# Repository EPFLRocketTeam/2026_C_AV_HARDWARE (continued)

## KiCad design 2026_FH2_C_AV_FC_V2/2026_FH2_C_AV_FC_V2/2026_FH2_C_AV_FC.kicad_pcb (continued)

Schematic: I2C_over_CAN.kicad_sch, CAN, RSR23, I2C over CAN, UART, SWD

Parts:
C57, C58, C59, C60, C61, C62, C63, C67, C68: 100n; C_0603_1608Metric; Mouser Part Number 581-06035C104JAT2A
C64: 2u2; C_0603_1608Metric; Mouser Part Number 581-06036D225K
C65, C66, C69, C70: 47p; C_0603_1608Metric; Mouser Part Number 581-06033A470GAT2A
D29: PESD4USB3UTBS; PESD4USB3UTBSQX; Mouser Part Number 771-PESD4USB3UTBS-QX
D31, D35: DESD2CAN2SOQ-7; SOT96P240X110-3N; Mouser Part Number 621-DESD2CAN2SOQ-7
R56, R57, R60, R63: 120; R_0603_1608Metric; Mouser Part Number 603-RC0603FR-13120RL
R58, R59: 33; R_0402_1005Metric; Mouser Part Number 603-RC0402FR-7D33RL
R61, R62: 33; R_0603_1608Metric; Mouser Part Number 603-RC0603FR-7W33RL
R76: 10k; R_0603_1608Metric; Mouser Part Number 603-AC0603FRE0710KL
TP5: CANSDAL; TestPoint_THTPad_1.0x1.0mm_Drill0.5mm
TP6: CANSCLL; TestPoint_THTPad_1.0x1.0mm_Drill0.5mm
TP7: CANSDAH; TestPoint_THTPad_1.0x1.0mm_Drill0.5mm
TP8: CANSCLH; TestPoint_THTPad_1.0x1.0mm_Drill0.5mm
TP9: SCL; TestPoint_THTPad_1.0x1.0mm_Drill0.5mm
TP10: SDA; TestPoint_THTPad_1.0x1.0mm_Drill0.5mm
TP11, TP13: CANH; TestPoint_THTPad_1.0x1.0mm_Drill0.5mm
TP12, TP14: CANL; TestPoint_THTPad_1.0x1.0mm_Drill0.5mm
U12: MAX3226; SSOP-16_5.3x6.2mm_P0.65mm; Mouser Part Number 700-MAX3226EAET
U13: SPINE_LT3960; LT3960; Mouser Part Number 584-LT3960EMSE#PBF; Mouser ID 584-LT3960EMSE#PBF
U14, U15: MCP2542FDxMF; DFN-8-1EP_3x3mm_P0.65mm_EP1.55x2.4mm; Mouser Part Number 579-MCP2542FD-E/MF

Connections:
+3V3: C58.1, C62.2, C64.1, C67.2, R76.2, U12.15 (VCC), U12.16 (~FORCEOFF), U13.6 (VIN), U13.8 (VCC), U14.5 (VIO), U15.5 (VIO); also elsewhere on the board
+5V: C63.1, C68.1, U14.3 (VDD), U15.3 (VDD); also elsewhere on the board
/Project Architecture/CAN RS232 and other connections/CAN1_H: C66.1, D31.1, R60.2, TP11.1, U14.7 (CANH); also elsewhere on the board
/Project Architecture/CAN RS232 and other connections/CAN1_L: C65.1, D31.2, R60.1, TP12.1, U14.6 (CANL); also elsewhere on the board
/Project Architecture/CAN RS232 and other connections/CAN2_H: C70.1, D35.1, R63.2, TP13.1, U15.7 (CANH); also elsewhere on the board
/Project Architecture/CAN RS232 and other connections/CAN2_L: C69.1, D35.2, R63.1, TP14.1, U15.6 (CANL); also elsewhere on the board
/Project Architecture/CAN RS232 and other connections/CANSCLH: D29.4, D29.7, R57.2, TP8.1, U13.4 (CANSCLH); also elsewhere on the board
/Project Architecture/CAN RS232 and other connections/CANSCLL: D29.5, D29.6, R57.1, TP6.1, U13.5 (CANSCLL); also elsewhere on the board
/Project Architecture/CAN RS232 and other connections/CANSDAH: D29.2, D29.9, R56.1, TP7.1, U13.2 (CANSDAH); also elsewhere on the board
/Project Architecture/CAN RS232 and other connections/CANSDAL: D29.1, D29.10, R56.2, TP5.1, U13.1 (CANSDAL); also elsewhere on the board
/Project Architecture/CAN RS232 and other connections/CAN_RX_1: R59.1; also elsewhere on the board
/Project Architecture/CAN RS232 and other connections/CAN_RX_2: R62.1; also elsewhere on the board
/Project Architecture/CAN RS232 and other connections/CAN_TX_1: R58.1; also elsewhere on the board
/Project Architecture/CAN RS232 and other connections/CAN_TX_2: R61.1; also elsewhere on the board
/Project Architecture/CAN RS232 and other connections/RX_RS232: U12.8 (R1IN); also elsewhere on the board
/Project Architecture/CAN RS232 and other connections/SCL: TP9.1, U13.9 (SCL); also elsewhere on the board
/Project Architecture/CAN RS232 and other connections/SDA: TP10.1, U13.10 (SDA); also elsewhere on the board
/Project Architecture/CAN RS232 and other connections/TX_RS232: U12.13 (T1OUT); also elsewhere on the board
/Project Architecture/CAN RS232 and other connections/rx_uart: U12.9 (R1OUT); also elsewhere on the board
/Project Architecture/CAN RS232 and other connections/tx_uart: U12.11 (T1IN); also elsewhere on the board
GND: C58.2, C60.2, C61.2, C62.1, C63.2, C64.2, C65.2, C66.2, C67.1, C68.2, C69.2, C70.2, D29.3, D29.8, D31.3, D35.3, U12.12 (FORCEON), U12.14 (GND), U13.3 (GND), U13.11 (GND), U14.2 (VSS), U14.8 (STBY), U14.9 (VSS), U15.2 (VSS), U15.8 (STBY), U15.9 (VSS); also elsewhere on the board
unnamed: C57.1, U12.2 (C1+)
unnamed: C57.2, U12.4 (C1-)
unnamed: C59.1, U12.5 (C2+)
unnamed: C59.2, U12.6 (C2-)
unnamed: C61.1, U12.3 (V+)
unnamed: C60.1, U12.7 (V-)
unnamed: R76.1, U13.7 (EN/MODE)
unnamed: R59.2, U14.4 (RXD)
unnamed: R58.2, U14.1 (TXD)
unnamed: R62.2, U15.4 (RXD)
unnamed: R61.2, U15.1 (TXD)

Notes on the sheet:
keep CAN short, the RX and TX can be longer
put close to spine
BUS protection
Labels
DESIGN NOTES: The UART header will be left floating most of the time, so configure: - RX internal pull-up - TX no pull-up
UART to RS232 IC
I2C over CAN transciever
CAN buses : INTRANET & CAMERAS
DESIGN NOTES: EN/MODE = FLOAT -> Slave EN/MODE = HIGH -> Master

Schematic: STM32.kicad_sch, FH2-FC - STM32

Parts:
BZ1: Buzzer; Buzzer_TDK_PS1240P02BT_D12.2mm_H6.5mm
C20: 10u; C_0603_1608Metric; Mouser Part Number 581-KGM15CR50J106MT
C21, C22, C23, C24, C26, C27, C28, C29, C31, C32, C33, C34, C35: 100n; C_0402_1005Metric; Mouser Part Number 581-KGM05CR71H104KH
C25, C77: 12pf; C_0402_1005Metric; Mouser Part Number 581-04025A120F4T2A
C30, C40, C41, C42: 100n; C_0603_1608Metric; Mouser Part Number 581-06035C104JAT2A
C36: 10n; C_0603_1608Metric; Mouser Part Number 581-06035C103J
C37, C38: 1u; C_0603_1608Metric; Mouser Part Number 581-0603YD105KAT4A
C39: 47p; C_0603_1608Metric; Mouser Part Number 581-06033A470GAT2A
C75, C76: 2u2; C_0603_1608Metric; Mouser Part Number 581-06036D225K
D9: RED; LED_0603_1608Metric
D10: GREEN; LED_0603_1608Metric
D11: 1N5819; D_SOD-123; Mouser Part Number 621-1N5819HWQ-7-F
FB1: 120R; L_0603_1608Metric; Mouser Part Number 810-MPZ1608S121ATDH5
J7: Conn_01x05; PinHeader_1x05_P2.54mm_Vertical_SMD_Pin1Left; Mouser Part Number 649-1012938090501BLF
Q1: IRLML0040TRPBF; SOT95P237X112-3N; Mouser Part Number 942-IRLML0040TRPBF
R9, R12, R13: 1k1; R_0603_1608Metric; Mouser Part Number 603-RT0603FRE071K1L
R11, R77: 10k; R_0603_1608Metric; Mouser Part Number 603-AC0603FRE0710KL
R14, R15, R16, R17, R19: 5k; R_0603_1608Metric; Mouser Part Number 603-AF0603DR-074K99L
R18: 33; R_0603_1608Metric; Mouser Part Number 603-RC0603FR-7W33RL
R20: 120; R_0603_1608Metric; Mouser Part Number 603-RC0603FR-13120RL
R21: 100k; R_0603_1608Metric; Mouser Part Number 603-SR0603FR-07100KL
SW1: SW_SPDT; B-TYPE; Mouser Part Number 229-CJS-1200TB
SW2: B3U-1000P; Mouser Part Number 653-B3U-1000P
U3: STM32H743ZIT6; LQFP-144_20x20mm_P0.5mm; Mouser Part Number 511-STM32H743ZIT6
U4, U5, U6: RGB; NEW_RGB_LED; Mouser Part Number 859-LTST-E133CEGBK
Y1: 16MHz; Crystal_SMD_Abracon_ABM3B-4Pin_5.0x3.2mm; Mouser Part Number 815-ABM3B-16-T

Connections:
+3.3VA: C36.1, C37.1, FB1.1, U3.33 (VDDA)
+3V3: C20.1, C21.1, C22.1, C23.1, C24.1, C26.1, C27.1, C28.1, C29.1, C31.1, C32.1, C33.1, C34.1, C35.1, C38.1, FB1.2, J7.1, R14.2, R15.2, R16.2, R17.2, R77.2, SW1.3 (C), U3.6 (VBAT), U3.17 (VDD), U3.30 (VDD), U3.39 (VDD), U3.52 (VDD), U3.62 (VDD), U3.72 (VDD), U3.84 (VDD), U3.95 (VDD33_USB), U3.108 (VDD), U3.121 (VDD), U3.131 (VDD), U3.144 (VDD); also elsewhere on the board
+5V: BZ1.1 (+), C40.2, C41.2, C42.2, D11.1 (K), U4.1 (VDD), U5.1 (VDD), U6.1 (VDD); also elsewhere on the board
/Project Architecture/ADXL375_and_TMP1075N/ALERT: U3.77 (PD8); also elsewhere on the board
/Project Architecture/ADXL375_and_TMP1075N/INT1: U3.56 (PG0); also elsewhere on the board
/Project Architecture/ADXL375_and_TMP1075N/SCL: R15.1, U3.54 (PF14); also elsewhere on the board
/Project Architecture/ADXL375_and_TMP1075N/SDA: R17.1, U3.55 (PF15); also elsewhere on the board
/Project Architecture/BMP390/BMP_ERROR_LED: U3.133 (PB3); also elsewhere on the board
/Project Architecture/BMP390/BMP_READY_LED: U3.137 (PB7); also elsewhere on the board
/Project Architecture/BMP390/CS1: U3.49 (PF11); also elsewhere on the board
/Project Architecture/BMP390/CS2: U3.44 (PC4); also elsewhere on the board
/Project Architecture/BMP390/CS3: U3.59 (PE8); also elsewhere on the board
/Project Architecture/BMP390/CS4: U3.57 (PG1); also elsewhere on the board
/Project Architecture/BMP390/INT1: U3.50 (PF12); also elsewhere on the board
/Project Architecture/BMP390/INT2: U3.45 (PC5); also elsewhere on the board
/Project Architecture/BMP390/INT3: U3.60 (PE9); also elsewhere on the board
/Project Architecture/BMP390/INT4: U3.58 (PE7); also elsewhere on the board
/Project Architecture/BMP390/MISO1: U3.20 (PF8); also elsewhere on the board
/Project Architecture/BMP390/MISO2: U3.4 (PE5); also elsewhere on the board
/Project Architecture/BMP390/MOSI1: U3.21 (PF9); also elsewhere on the board
/Project Architecture/BMP390/MOSI2: U3.5 (PE6); also elsewhere on the board
/Project Architecture/BMP390/SCK1: U3.19 (PF7); also elsewhere on the board
/Project Architecture/BMP390/SCK2: U3.1 (PE2); also elsewhere on the board
/Project Architecture/CAN RS232 and other connections/CAN_RX_1: U3.114 (PD0); also elsewhere on the board
/Project Architecture/CAN RS232 and other connections/CAN_RX_2: U3.73 (PB12); also elsewhere on the board
/Project Architecture/CAN RS232 and other connections/CAN_TX_1: U3.115 (PD1); also elsewhere on the board
/Project Architecture/CAN RS232 and other connections/CAN_TX_2: U3.74 (PB13); also elsewhere on the board
/Project Architecture/CAN RS232 and other connections/SCL: R16.1, U3.11 (PF1); also elsewhere on the board
/Project Architecture/CAN RS232 and other connections/SDA: R14.1, U3.10 (PF0); also elsewhere on the board
/Project Architecture/CAN RS232 and other connections/rx_uart: U3.35 (PA1); also elsewhere on the board
/Project Architecture/CAN RS232 and other connections/tx_uart: U3.34 (PA0); also elsewhere on the board
/Project Architecture/GNSS MAX-M10S/EXINT: U3.89 (PG4); also elsewhere on the board
/Project Architecture/GNSS MAX-M10S/GNSS_ERROR_LED: U3.82 (PD13); also elsewhere on the board
/Project Architecture/GNSS MAX-M10S/GNSS_READY_LED: U3.81 (PD12); also elsewhere on the board
/Project Architecture/GNSS MAX-M10S/RST: U3.88 (PG3); also elsewhere on the board
/Project Architecture/GNSS MAX-M10S/RX: U3.96 (PC6); also elsewhere on the board
/Project Architecture/GNSS MAX-M10S/TIMEPULSE: U3.87 (PG2); also elsewhere on the board
/Project Architecture/GNSS MAX-M10S/TX: U3.97 (PC7); also elsewhere on the board
/Project Architecture/ICM-45605/CS1: U3.65 (PE12); also elsewhere on the board
/Project Architecture/ICM-45605/CS2: U3.79 (PD10); also elsewhere on the board
/Project Architecture/ICM-45605/CS3: U3.80 (PD11); also elsewhere on the board
/Project Architecture/ICM-45605/CS4: U3.67 (PE14); also elsewhere on the board
/Project Architecture/ICM-45605/FSYNC: U3.85 (PD14); also elsewhere on the board
/Project Architecture/ICM-45605/ICM_ERROR_LED: U3.132 (PG15); also elsewhere on the board
/Project Architecture/ICM-45605/ICM_READY_LED: U3.134 (PB4); also elsewhere on the board
/Project Architecture/ICM-45605/INT1: U3.66 (PE13); also elsewhere on the board
/Project Architecture/ICM-45605/INT2: U3.64 (PE11); also elsewhere on the board
/Project Architecture/ICM-45605/INT3: U3.63 (PE10); also elsewhere on the board
/Project Architecture/ICM-45605/INT4: U3.68 (PE15); also elsewhere on the board
/Project Architecture/MicroSD/SD_CARD_IN: U3.122 (PD6); also elsewhere on the board
/Project Architecture/MicroSD/SD_CARD_IN_LED: U3.102 (PA10); also elsewhere on the board
/Project Architecture/MicroSD/SD_CLK: U3.113 (PC12); also elsewhere on the board
/Project Architecture/MicroSD/SD_CMD: U3.116 (PD2); also elsewhere on the board
/Project Architecture/MicroSD/SD_DAT0: U3.98 (PC8); also elsewhere on the board
/Project Architecture/MicroSD/SD_DAT1: U3.99 (PC9); also elsewhere on the board
/Project Architecture/MicroSD/SD_DAT2: U3.111 (PC10); also elsewhere on the board
/Project Architecture/MicroSD/SD_DAT3: U3.112 (PC11); also elsewhere on the board
/Project Architecture/POWER/PWRGD3V3: U3.139 (PB8); also elsewhere on the board
/Project Architecture/Pyro/Mux_S1: U3.125 (PG10); also elsewhere on the board
/Project Architecture/Pyro/Mux_S2: U3.126 (PG11); also elsewhere on the board
/Project Architecture/Pyro/PYRO1: U3.9 (PC15); also elsewhere on the board
/Project Architecture/Pyro/PYRO2: U3.8 (PC14); also elsewhere on the board
/Project Architecture/Pyro/PYRO3: U3.142 (PE1); also elsewhere on the board
/Project Architecture/Pyro/PYRO4: U3.141 (PE0); also elsewhere on the board
/Project Architecture/Pyro/PYRO_active: U3.26 (PC0); also elsewhere on the board
/Project Architecture/Pyro/v_adc: U3.29 (PC3_C); also elsewhere on the board
/Project Architecture/SPINE/GPIO_RFM_RX_INT0: U3.47 (PB1); also elsewhere on the board
/Project Architecture/SPINE/GPIO_RFM_RX_RST: U3.46 (PB0); also elsewhere on the board
/Project Architecture/SPINE/GPIO_RFM_TX_INT0: U3.37 (PA3); also elsewhere on the board
/Project Architecture/SPINE/GPIO_RFM_TX_RST: U3.36 (PA2); also elsewhere on the board
/Project Architecture/SPINE/SPI_RFM_RX_CLK: U3.69 (PB10); also elsewhere on the board
/Project Architecture/SPINE/SPI_RFM_RX_CS: U3.48 (PB2); also elsewhere on the board
/Project Architecture/SPINE/SPI_RFM_RX_MISO: U3.28 (PC2_C); also elsewhere on the board
/Project Architecture/SPINE/SPI_RFM_RX_MOSI: U3.27 (PC1); also elsewhere on the board
/Project Architecture/SPINE/SPI_RFM_TX_CLK: U3.41 (PA5); also elsewhere on the board
/Project Architecture/SPINE/SPI_RFM_TX_CS: U3.40 (PA4); also elsewhere on the board
/Project Architecture/SPINE/SPI_RFM_TX_MISO: U3.42 (PA6); also elsewhere on the board
/Project Architecture/SPINE/SPI_RFM_TX_MOSI: U3.43 (PA7); also elsewhere on the board
/Project Architecture/STM32/BOOT0: R11.2, U3.138 (BOOT0)
/Project Architecture/STM32/BUZZ-: BZ1.2 (-), D11.2 (A), Q1.3 (D)
/Project Architecture/STM32/BUZZER: R20.1, U3.70 (PB11)
/Project Architecture/STM32/LEDCTRL: R18.1, U3.127 (PG12)
/Project Architecture/STM32/LEDDATA1: C39.2, R18.2, R19.1, U4.2 (DIN)
/Project Architecture/STM32/NRST: C30.1, D9.2 (A), J7.4, R77.1, SW2.2, U3.25 (NRST)
/Project Architecture/STM32/NRST_K: D9.1 (K), R12.1
/Project Architecture/STM32/RCC_IN: C25.1, U3.23 (PH0), Y1.1
/Project Architecture/STM32/RCC_OUT: R9.2, U3.24 (PH1)
/Project Architecture/STM32/SWDCLK: J7.3, U3.109 (PA14)
/Project Architecture/STM32/SWDIO: J7.2, U3.105 (PA13)
/Project Architecture/STM32/SW_BOOT0: D10.2 (A), R11.1, SW1.2 (B)
/Project Architecture/STM32/SW_BOOT0_K: D10.1 (K), R13.1
/Project Architecture/USB B/D1+: U3.104 (PA12); also elsewhere on the board
/Project Architecture/USB B/D1-: U3.103 (PA11); also elsewhere on the board
/Project Architecture/USB B/D2+: U3.76 (PB15); also elsewhere on the board
/Project Architecture/USB B/D2-: U3.75 (PB14); also elsewhere on the board
GND: C20.2, C21.2, C22.2, C23.2, C24.2, C25.2, C26.2, C27.2, C28.2, C29.2, C30.2, C31.2, C32.2, C33.2, C34.2, C35.2, C36.2, C37.2, C38.2, C39.1, C40.1, C41.1, C42.1, C75.2, C76.2, C77.2, J7.5, Q1.2 (S), R12.2, R13.2, R19.2, R21.2, SW1.1 (A), SW2.1, U3.16 (VSS), U3.31 (VSSA), U3.38 (VSS), U3.51 (VSS), U3.61 (VSS), U3.83 (VSS), U3.94 (VSS), U3.107 (VSS), U3.120 (VSS), U3.130 (VSS), U4.3 (VSS), U5.3 (VSS), U6.3 (VSS), Y1.2, Y1.4; also elsewhere on the board
unnamed: C75.1, U3.106 (VCAP)
unnamed: C76.1, U3.71 (VCAP)
unnamed: C77.1, R9.1, Y1.3
unnamed: Q1.1 (G), R20.2, R21.1
unnamed: U4.4 (DOUT), U5.2 (DIN)
unnamed: U5.4 (DOUT), U6.2 (DIN)

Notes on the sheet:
1VBAT, 11VDD, 1VDD33_USB. One 100n cap for each. So 13 100n caps + one bulk cap
STM32
BOOT and NRST switches
16MHz Crystal Oscillator
f=1/(2*PI*R*C)~ 100MHz
Flyback bc inductive
DESIGN NOTES: CL1,2 = 2(CL - Cs) RExt = 1 / (2 π F CL2) With F = 16MHz, and CL2 = 12pF, Rext ~ 1k If the crystal doesn't start, reduce Rext (replace with 0Ohmes)
Note : when BOOT0 is pulled high, it enables UART, USB or I2C to program the MC. Basically being able to flash in a program. If BOOT0 is low, it will run the onboard program
Specs: - F = 16 MHz - CL = 10 pF - TEMP: -10° -> 60° - ESR = 50 Ohmes
Note : Negative RST or NRST resets when at logic 0. It is pulled high by default, so it could be left floating with a 100n decoupling cap
SWD Debug header
MOSFET to drive Buz bc of needed current
RC Filter
Ferrite Bead: 120Ohms @ 100MHz
Pull-Down
DESIGN NOTES: Keep the clock traces very short, ideally around 1cm for PHY and STM32. Choice of crystal: 1. Since we don't have a really tight constraint on size, its best to go for a larger footprint to have the smallest ESR possible (small ESR = faster startup time) 2. Higher Load Capacitance are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

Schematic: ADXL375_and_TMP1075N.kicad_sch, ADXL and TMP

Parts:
C71, C73: 100n; C_0603_1608Metric; Mouser Part Number 581-06035C104JAT2A
C74: 10n; C_0603_1608Metric; Mouser Part Number 581-06035C103J
C78: TAJA106K016RNJV; CAPPM3216X180N; Mouser Part Number 581-TAJA106K016RNJV
IC8: ADXL375BCCZ; CC-14-1; Mouser Part Number 584-ADXL375BCCZ
R64: 5k; R_0603_1608Metric; Mouser Part Number 603-AF0603DR-074K99L
U16: TMP1075DSG; WSON-8-1EP_2x2mm_P0.5mm_EP0.9x1.6mm_ThermalVias; Mouser Part Number 595-TMP1075DSGR

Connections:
+3V3: C71.1, C73.1, C74.1, C78.1 (+), IC8.1 (VDD_I/O), IC8.6 (VS), IC8.7 (~CS), IC8.12 (SDO/ALT_ADDRESS), R64.1, U16.5 (A2), U16.6 (A1), U16.8 (V+); also elsewhere on the board
/Project Architecture/ADXL375_and_TMP1075N/ALERT: R64.2, U16.3 (ALERT); also elsewhere on the board
/Project Architecture/ADXL375_and_TMP1075N/INT1: IC8.8 (INT1); also elsewhere on the board
/Project Architecture/ADXL375_and_TMP1075N/SCL: IC8.14 (SCL/SCLK), U16.2 (SCL); also elsewhere on the board
/Project Architecture/ADXL375_and_TMP1075N/SDA: IC8.13 (SDA/DO/SDIO), U16.1 (SDA); also elsewhere on the board
GND: C71.2, C73.2, C74.2, C78.2 (-), IC8.2 (GND_1), IC8.4 (GND_2), IC8.5 (GND_3), U16.4 (GND), U16.7 (A0), U16.9 (EP); also elsewhere on the board

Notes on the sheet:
Close to VDD_I/O
TMP0175N
ADXL375
Labels
DESIGN NOTES: Adresse i2c: 0x4f (cf doc page 14)
DESIGN NOTES: Physically place the ADXL close to a mounting point to prevent undampened vibrations
DESIGN NOTES: The Alert pin should be configured in comparator mode ( TM=0, POL=0): it's a open drain output that will be driven to low(~0.15V) when the temperature exceeds T-HIGH.
DESIGN NOTES: The TMP1075DSG is the TMP1075, not to be confused with the TMP1075N which does not have the A1 and A2 pins.
in stm32cubeIDE i didn't have enough interrupt pins for ALERT. So I chose to connect it to a GPIO_OUTPUT. You can poll the Alert pin every second per say.
DESIGN NOTES: CS high = i2c mode ALT high => i2c adress = 0x1D Write adress = 0x3A Read adress = 0x3B

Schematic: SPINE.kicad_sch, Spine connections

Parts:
J11: DIN41612_02x16_AB; DIN41612_B2_2x16_Male_Horizontal_THT

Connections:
+24V: J11.a15, J11.a16, J11.b15, J11.b16; also elsewhere on the board
/Project Architecture/CAN RS232 and other connections/CAN1_H: J11.a1; also elsewhere on the board
/Project Architecture/CAN RS232 and other connections/CAN1_L: J11.b1; also elsewhere on the board
/Project Architecture/CAN RS232 and other connections/CAN2_H: J11.a2; also elsewhere on the board
/Project Architecture/CAN RS232 and other connections/CAN2_L: J11.b2; also elsewhere on the board
/Project Architecture/CAN RS232 and other connections/CANSCLH: J11.a12; also elsewhere on the board
/Project Architecture/CAN RS232 and other connections/CANSCLL: J11.b12; also elsewhere on the board
/Project Architecture/CAN RS232 and other connections/CANSDAH: J11.a11; also elsewhere on the board
/Project Architecture/CAN RS232 and other connections/CANSDAL: J11.b11; also elsewhere on the board
/Project Architecture/CAN RS232 and other connections/RX_RS232: J11.a10; also elsewhere on the board
/Project Architecture/CAN RS232 and other connections/TX_RS232: J11.b10; also elsewhere on the board
/Project Architecture/POWER/+5V_SPINE: J11.a14, J11.b14; also elsewhere on the board
/Project Architecture/SPINE/GPIO_RFM_RX_INT0: J11.a5; also elsewhere on the board
/Project Architecture/SPINE/GPIO_RFM_RX_RST: J11.b5; also elsewhere on the board
/Project Architecture/SPINE/GPIO_RFM_TX_INT0: J11.a8; also elsewhere on the board
/Project Architecture/SPINE/GPIO_RFM_TX_RST: J11.b8; also elsewhere on the board
/Project Architecture/SPINE/SPI_RFM_RX_CLK: J11.b4; also elsewhere on the board
/Project Architecture/SPINE/SPI_RFM_RX_CS: J11.a4; also elsewhere on the board
/Project Architecture/SPINE/SPI_RFM_RX_MISO: J11.b3; also elsewhere on the board
/Project Architecture/SPINE/SPI_RFM_RX_MOSI: J11.a3; also elsewhere on the board
/Project Architecture/SPINE/SPI_RFM_TX_CLK: J11.b7; also elsewhere on the board
/Project Architecture/SPINE/SPI_RFM_TX_CS: J11.a7; also elsewhere on the board
/Project Architecture/SPINE/SPI_RFM_TX_MISO: J11.b6; also elsewhere on the board
/Project Architecture/SPINE/SPI_RFM_TX_MOSI: J11.a6; also elsewhere on the board
GND: J11.a9, J11.a13, J11.b9, J11.b13; also elsewhere on the board

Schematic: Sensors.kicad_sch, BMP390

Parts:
C1, C2, C3, C4, C5, C6, C7, C8: 100n; C_0603_1608Metric; Mouser Part Number 581-06035C104JAT2A
D1: GREEN; LED_0603_1608Metric
D2: RED; LED_0603_1608Metric
IC1, IC2, IC3, IC4: BMP390; Mouser Part Number 262-BMP390
R1, R2: 1k1; R_0603_1608Metric; Mouser Part Number 603-RT0603FRE071K1L

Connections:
+3V3: C1.1, C2.1, C3.1, C4.1, C5.1, C6.1, C7.1, C8.1, IC1.1 (VDDIO), IC1.10 (VDD), IC2.1 (VDDIO), IC2.10 (VDD), IC3.1 (VDDIO), IC3.10 (VDD), IC4.1 (VDDIO), IC4.10 (VDD); also elsewhere on the board
/Project Architecture/BMP390/BMP_ERROR_LED: D2.2 (A); also elsewhere on the board
/Project Architecture/BMP390/BMP_READY_LED: D1.2 (A); also elsewhere on the board
/Project Architecture/BMP390/CS1: IC1.6 (CSB); also elsewhere on the board
/Project Architecture/BMP390/CS2: IC3.6 (CSB); also elsewhere on the board
/Project Architecture/BMP390/CS3: IC2.6 (CSB); also elsewhere on the board
/Project Architecture/BMP390/CS4: IC4.6 (CSB); also elsewhere on the board
/Project Architecture/BMP390/INT1: IC1.7 (INT); also elsewhere on the board
/Project Architecture/BMP390/INT2: IC3.7 (INT); also elsewhere on the board
/Project Architecture/BMP390/INT3: IC2.7 (INT); also elsewhere on the board
/Project Architecture/BMP390/INT4: IC4.7 (INT); also elsewhere on the board
/Project Architecture/BMP390/MISO1: IC1.5 (SDO), IC3.5 (SDO); also elsewhere on the board
/Project Architecture/BMP390/MISO2: IC2.5 (SDO), IC4.5 (SDO); also elsewhere on the board
/Project Architecture/BMP390/MOSI1: IC1.4 (SDI), IC3.4 (SDI); also elsewhere on the board
/Project Architecture/BMP390/MOSI2: IC2.4 (SDI), IC4.4 (SDI); also elsewhere on the board
/Project Architecture/BMP390/SCK1: IC1.2 (SCK), IC3.2 (SCK); also elsewhere on the board
/Project Architecture/BMP390/SCK2: IC2.2 (SCK), IC4.2 (SCK); also elsewhere on the board
GND: C1.2, C2.2, C3.2, C4.2, C5.2, C6.2, C7.2, C8.2, IC1.3 (VSS_1), IC1.8 (VSS_2), IC1.9 (VSS_3), IC2.3 (VSS_1), IC2.8 (VSS_2), IC2.9 (VSS_3), IC3.3 (VSS_1), IC3.8 (VSS_2), IC3.9 (VSS_3), IC4.3 (VSS_1), IC4.8 (VSS_2), IC4.9 (VSS_3), R1.2, R2.2; also elsewhere on the board
unnamed: D1.1 (K), R1.1
unnamed: D2.1 (K), R2.1

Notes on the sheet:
BMP390 #3
BMP390 #1
BMP390 #2
BMP390
BMP390 #4
SENSORS
DESIGN NOTES: In case of SPI malfunction, the 4 sensors are divided in two buses, sensors 1,2 have one bus, and sensors 3,4 have another bus.
Labels
DESIGN NOTES: The datasheet mentions SDI and SDO, the equivalents are: SDI = MOSI SDO = MISO

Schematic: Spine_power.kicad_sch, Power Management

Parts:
C9, C12, C13: 4u7; C_0603_1608Metric; Mouser Part Number 581-KGM15BR50J475KT
C10: 1000p; C_0603_1608Metric; Mouser Part Number 581-06031A102JAT2A
C11, C15, C16, C17, C18, C19: 100n; C_0603_1608Metric; Mouser Part Number 581-06035C104JAT2A
C14: 1u; C_0603_1608Metric; Mouser Part Number 581-0603YD105KAT4A
D3: SMF5V0A; D_SOD-123; Mouser Part Number 576-SMF5.0A
D5, D6, D8, D25, D30: RED; LED_0603_1608Metric
F2, F3: 1206L075_16WR; L_1206_3216Metric; Mouser Part Number 576-1206L075/16WR
H1, H2, H3, H4: MountingHole_Pad; MountingHole_3.2mm_M3_DIN965_Pad
IC5, IC6, IC7: TPS22919DCKR; SOT65P210X110-6N; Mouser Part Number 595-TPS22919DCKR
R3: 100k; R_0603_1608Metric; Mouser Part Number 603-SR0603FR-07100KL
R4, R6, R10, R79, R80: 1k1; R_0603_1608Metric; Mouser Part Number 603-RT0603FRE071K1L
R7: 32k; R_0603_1608Metric; Mouser Part Number 603-RC0603FR-0732K4L
R8: 10k; R_0603_1608Metric; Mouser Part Number 603-AC0603FRE0710KL
TP1: +3V3; TestPoint_THTPad_1.0x1.0mm_Drill0.5mm
TP2: +5V_SPINE; TestPoint_THTPad_1.0x1.0mm_Drill0.5mm
TP3: +5V_VBUS; TestPoint_THTPad_1.0x1.0mm_Drill0.5mm
TP4: +5V; TestPoint_THTPad_1.0x1.0mm_Drill0.5mm
U1: MCP1727-3302xSN; SOIC-8_3.9x4.9mm_P1.27mm; Mouser Part Number 579-MCP1727-3302E/SN
U2: TPS2116DRL; SOT-583-8; Mouser Part Number 595-TPS2116DRLR

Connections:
+3V3: C14.1, R3.1, R10.2, TP1.1, U1.7 (Sense), U1.8 (Vout); also elsewhere on the board
+5V: C9.1, C19.2, R6.1, R79.2, TP4.1, U1.1 (Vin), U1.2 (Vin), U1.3 (~SHDN), U2.2 (VOUT), U2.7 (VOUT); also elsewhere on the board
/Project Architecture/POWER/+5V_SPINE: D3.1 (A1), IC5.1 (IN), IC5.3 (ON); also elsewhere on the board
/Project Architecture/POWER/+5V_SPINE_PWR: C12.1, C15.1, C17.1, D6.2 (A), IC5.5 (QOD), IC5.6 (OUT), R7.1, TP2.1, U2.3 (VIN1), U2.5 (MODE)
/Project Architecture/POWER/+5V_USB: C11.1, C13.1, C16.1, C18.1, D30.2 (A), IC6.5 (QOD), IC6.6 (OUT), IC7.5 (QOD), IC7.6 (OUT), TP3.1, U2.6 (VIN2)
/Project Architecture/POWER/PR1: R7.2, R8.1, U2.4 (PR1)
/Project Architecture/POWER/PWRGD3V3: R3.2, U1.5 (PWRGD); also elsewhere on the board
/Project Architecture/USB B/VBUS1: F2.1; also elsewhere on the board
/Project Architecture/USB B/VBUS2: F3.1; also elsewhere on the board
GND: C9.2, C10.2, C11.2, C12.2, C13.2, C14.2, C15.2, C16.2, C17.2, C18.2, C19.1, D3.2 (A2), D5.1 (K), D8.1 (K), H1.1, H2.1, H3.1, H4.1, IC5.2 (GND), IC6.2 (GND), IC7.2 (GND), R4.1, R8.2, R80.1, U1.4 (GND), U2.1 (GND); also elsewhere on the board
unnamed: D5.2 (A), R79.1
unnamed: D6.1 (K), R4.2
unnamed: D8.2 (A), R10.1
unnamed: D25.2 (A), R6.2
unnamed: D25.1 (K), U2.8 (ST)
unnamed: D30.1 (K), R80.2
unnamed: F2.2, IC6.1 (IN), IC6.3 (ON)
unnamed: F3.2, IC7.1 (IN), IC7.3 (ON)
unnamed: C10.1, U1.6 (Cdelay)

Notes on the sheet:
SPINE & POWER
ORing of the VBUS lines to then pass to the MUX
there is no tvs protection here because it is included in the usb eds protection diode on the USB B page
5V->3V3 LDO
DESIGN NOTES: tFALL = 2.2 × (RDIS || RL) × CL where R_DIS = R_QOD + R_PD R_QOD is 0 (cause shorted) and R_PD is the internal resistor. Shorted, cause CL value is pretty high (all of the capas on the board), so I don't want a larger fall time.
Regulate from 5V to 3.3V
DESIGN NOTES: Output current up to 1.5A safely Vdrop = Imax * R = 500mA * 125mOhmes = 62.5mV -> basically an ideal diode
Power MUX : Priority to SPINE, then VBUS
DESIGN NOTES: ST: Open drain status pin. Pulled low when VIN1 is not being used LED turns on if Vin2 is source
DESIGN NOTES: Vref = 1V (0.92-1.08) If PR1 > Vref -> Vin1 If PR1 < Vref -> Vin2 So VinCritical = (R1+R2)/(R2)*Vref = 4.2V So will switch to Vin2 if Vin1 < 4.2V
POWER inputs : filtering, line protection + ORing for VBUS lines (FS & HS)
The SHDN input is used to turn the LDO output voltage on and off. When the SHDN input is at a logic-high level, the LDO output voltage is enabled. When the SHDN input is pulled to a logic-low level, the LDO output voltage is disabled. When the SHDN input is pulled low, the PWRGD output also goes lo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

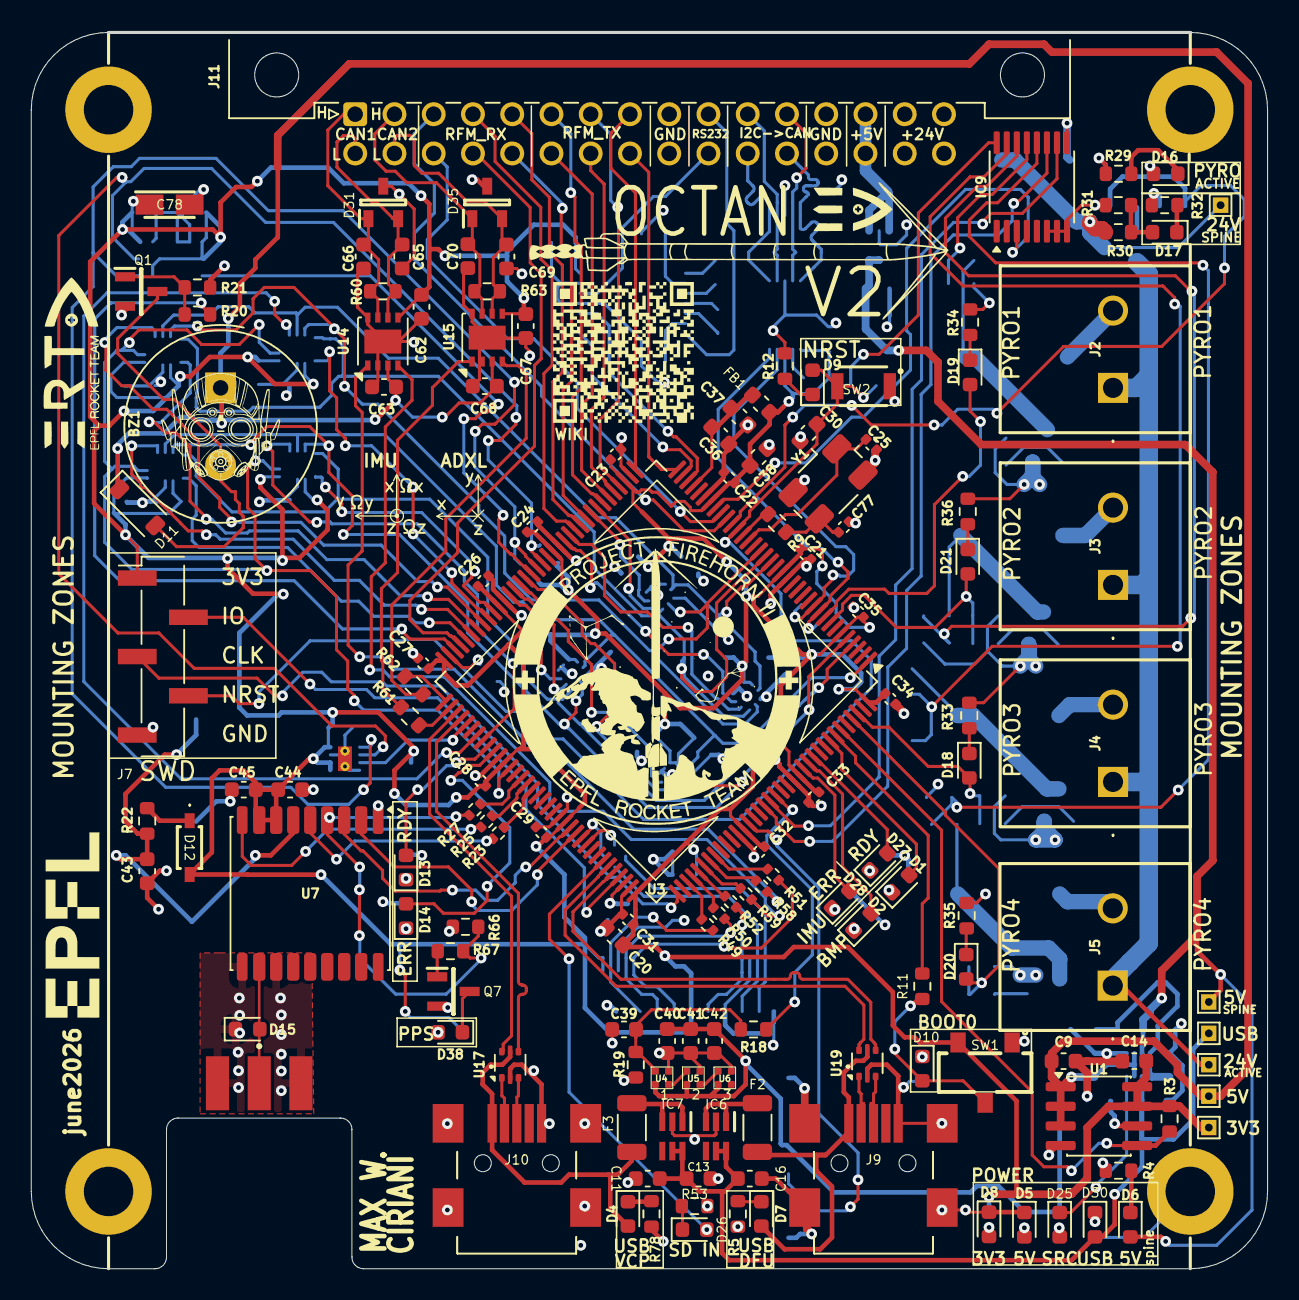
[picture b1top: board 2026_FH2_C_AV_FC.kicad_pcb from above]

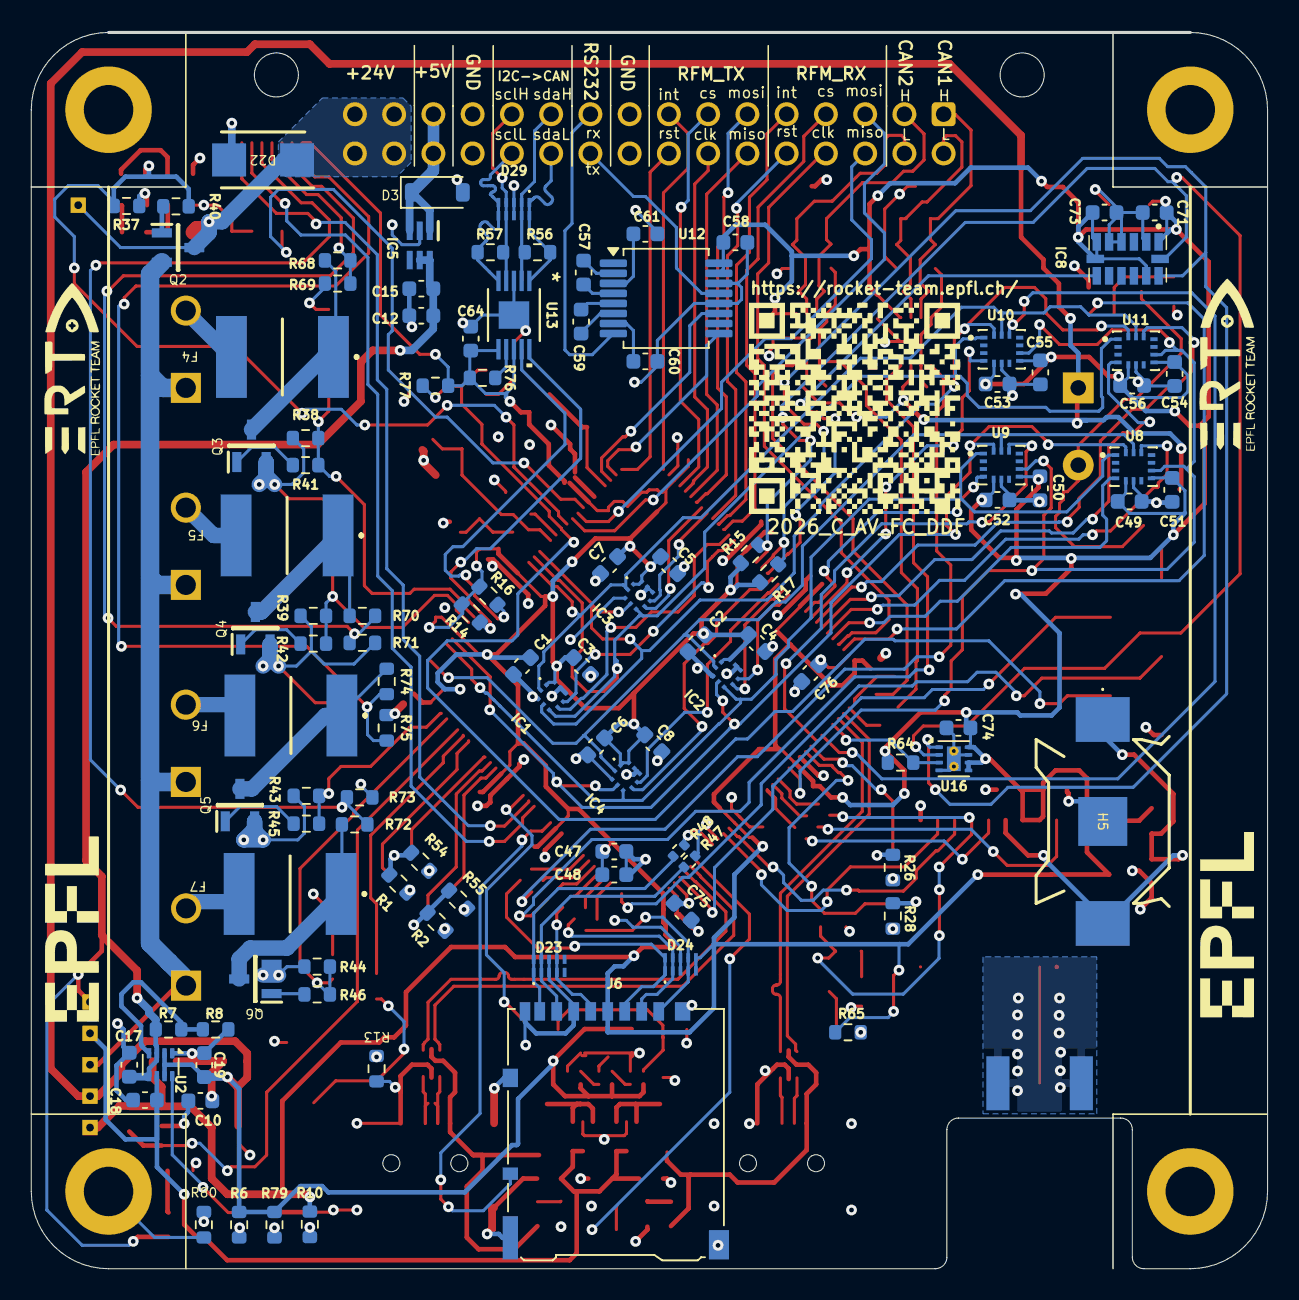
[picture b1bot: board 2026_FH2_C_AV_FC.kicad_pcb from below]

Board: 4 copper layers, 80.0 x 80.0 mm, 254 parts (108 on the bottom side), 192 nets.

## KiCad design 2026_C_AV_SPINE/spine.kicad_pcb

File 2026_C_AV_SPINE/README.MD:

# Firehorn II - Spine

<p>
  
  This repository contains the layout and schematics for the Spine on Firehorn.
  The goal of the spine on the rocket is to connect all the main components
  together like the Flight Computer, Telemetry Board and the Propulsion Computer.
  It also interface with the external power and the batteries onboard the rocket.
</p>
<br clear="all">

## External Resources

A reference to all the used resources to conceptualize, design and manufacture this board.

### ERT Specific Resources

Some resources might not be accesible to non-member.

-   [EPFL Rocket Team Wiki](https://rocket-team.epfl.ch/en/competition/Firehorn_2)
-   [Layout for the PINs of the DIN41612 Connectors](https://docs.google.com/spreadsheets/d/1EZ579WzLWqAGfyV8ViaIMcHjPTb54OhZBxatDAISEa4/edit?gid=0#gid=0)
-   [Power Sizing](https://docs.google.com/spreadsheets/d/1KNnJoExsyLhisfs7nwM8zVTQSHFLSJoFrzyELzKBYbc/edit?gid=0#gid=0)

### General Resources

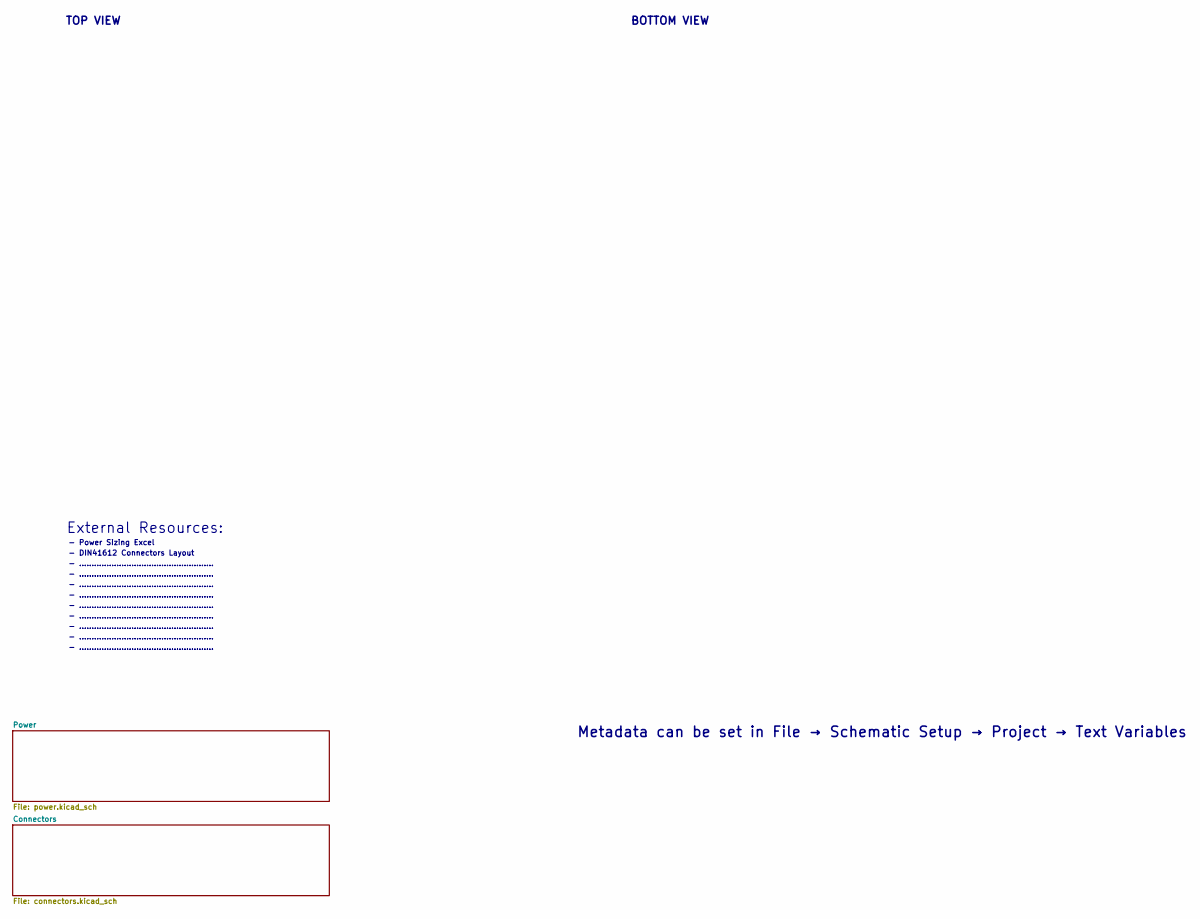
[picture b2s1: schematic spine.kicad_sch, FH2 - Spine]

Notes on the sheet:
- ......................................................
BOTTOM VIEW
External Resources:
- DIN41612 Connectors Layout
TOP VIEW
- Power Sizing Excel
Metadata can be set in File → Schematic Setup → Project → Text Variables
